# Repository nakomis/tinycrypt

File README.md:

# tinycrypt — a DIY FIDO2 security key you approve from your Apple Watch

## Support

If you find this useful, please consider buying me a coffee:

## Table of Contents

<!-- toc -->
<!-- tocstop -->

## Overview

A YubiKey-style FIDO2/WebAuthn USB security key built on an ESP32-S3, where the "touch the key"
step happens on your wrist instead: the key sends a push notification to an Apple Watch, you tap
**Approve**, and the watch proves it over Bluetooth before the key signs you in.

The first target is signing into AWS IAM Identity Center with the "Security key" MFA option.

**Hardware:**
- ESP32-S3 (target board: Waveshare ESP32-S3-Zero) — native USB, Wi-Fi, BLE
- Microchip ATECC608 — ECC P-256 secure element (I²C) for key storage, added after the software prototype
- Apple Watch — user-presence approval

**Status:** feasibility spikes. Spike A passed: an ESP32-S3 running the
[SoloKeys solo1](https://github.com/solokeys/solo1) CTAP2 core, with an insecure software key and a
BOOT-button presence check, registered and signed into IAM Identity Center from Chrome. The earlier
ATtiny85 / U2F experiments live on the [`spike`](https://github.com/nakomis/tinycrypt/tree/spike) branch.

## How it fits together

1. The browser asks the key (USB HID, CTAP2) for a WebAuthn assertion.
2. The key sends an approval request: AWS IoT Core → SNS → APNs → actionable watch notification (about 2 s).
3. You tap **Approve**; the watch connects to the key over BLE and signs a fresh nonce with its Secure Enclave key.
   The watch must be in Bluetooth range: a remote approval is impossible. On a real watch the Bluetooth exchange takes about 1.4 s after you tap.
4. The key verifies the watch's signature, then signs the WebAuthn assertion and returns it to the browser.

The firmware is split into a portable CTAP2 core with swappable transport, crypto, presence and
notifier back ends, so most of it also runs as a simulator on macOS.

> **Testing builds** can use a software key instead of the ATECC608. That build is deliberately
> insecure, is for testing only, and must only ever be registered against a read-only test user.

## Building and testing

All the firmware lives in `embedded/`, and the commands below run from there. The CTAP2 core is
[SoloKeys solo1](https://github.com/solokeys/solo1) (Apache-2.0 OR MIT), pinned as a submodule in
`embedded/third_party/solo1` under its own licence. Fetch it and the libraries it builds:

```bash
cd embedded
git submodule update --init third_party/solo1
git -C third_party/solo1 submodule update --init crypto/cifra crypto/micro-ecc crypto/tiny-AES-c tinycbor
```

| Path (under `embedded/`) | What it is |
|---|---|
| `cmake/solo_sources.cmake` | The core's source list, shared by both builds |
| `port/` | Portable code: the secure-element interface and solo1's crypto routed through it, presence, the soft element (`TINYCRYPT_INSECURE_SOFT_KEY`, refused in release builds) |
| `sim/` | Mac simulator: CTAPHID over UDP, state in a directory |
| `esp32s3/` | ESP-IDF firmware: TinyUSB FIDO HID, the ATECC608B (or the soft element in NVS), presence, the provisioner |
| `tests/` | python-fido2 tests against the sim, plus `hw_smoke.py` for a real key |

**Mac sim** (needs `brew install libsodium`):

```bash
cmake -S . -B build -DTINYCRYPT_INSECURE_SOFT_KEY=ON && cmake --build build
python3 -m venv tests/.venv && tests/.venv/bin/pip install -r tests/requirements.txt
tests/.venv/bin/python -m pytest tests
build/tinycrypt-sim --presence prompt     # run it by hand; press Enter to approve
```

**ESP32-S3** (ESP-IDF 5.5 in `~/esp/v5.5/esp-idf`):

```bash
esp32s3/build.sh                                    # build (KEYSTORE=atecc for the ATECC608B; soft by default)
esp32s3/build.sh -p /dev/cu.usbmodemXXXX flash      # flash over the UART port
esp32s3/flash-manual.sh /dev/cu.usbmodemXXXX        # if auto-reset fails: hold BOOT, tap RST, release BOOT first
tests/.venv/bin/python tests/hw_smoke.py            # register + authenticate; press BOOT when asked
```

The key enumerates on the S3's **native** USB port (not the UART one) as
"tinycrypt INSECURE TEST KEY", USB ID 303a:4004.

**ATECC608B** (CRYPT-22). Wire a breakout to the dev board: VCC to 3V3, GND, SDA to GPIO38, SCL to
GPIO21 (the PCB's pins; change them under esp-cryptoauthlib in `esp32s3/build.sh menuconfig`). The
breakouts have their own pull-ups. A blank chip answers at 0xC0 (8-bit); the M5Stack Trust&GO unit
(0x6A) is factory-locked and can't take tinycrypt's configuration. Locking is permanent: do a
sacrificial chip first. The provisioner's console is the **native** USB port (USB-Serial-JTAG), so
connect that one; flashing it and the key image straight after needs no BOOT+RST.

```bash
KEYSTORE=atecc esp32s3/build.sh provisioner                 # the provisioner image
ESPTOOL_BEFORE=default_reset esp32s3/flash-manual.sh --provisioner /dev/cu.usbmodemXXXX  # else BOOT+RST first
esp32s3/tools/atecc_provision.py /dev/cu.usbmodemXXXX info
esp32s3/tools/atecc_provision.py /dev/cu.usbmodemXXXX lock  # PERMANENT; asks for the serial
esp32s3/tools/atecc_provision.py /dev/cu.usbmodemXXXX csr tinycrypt-sandbox-key-1 /tmp/key-1.csr
infra/scripts/provision-key.sh key-1 --csr /tmp/key-1.csr   # certificate from the chip's own key
KEYSTORE=atecc esp32s3/build.sh && ESPTOOL_BEFORE=default_reset esp32s3/flash-manual.sh /dev/cu.usbmodemXXXX   # the key again
```

The same steps with the default soft keystore move a key's IoT private key out of `prov` into its
(INSECURE) soft element, with no chip.

## Architecture Diagram

`docs/architecture/tinycrypt.drawio` will be the source for the architecture diagram; the SVG is
auto-regenerated on commit by the pre-commit hook in `.githooks/pre-commit`.

To activate the hook after cloning:

```bash
git config core.hooksPath .githooks
```

## Support

If you find this useful, please consider buying me a coffee:

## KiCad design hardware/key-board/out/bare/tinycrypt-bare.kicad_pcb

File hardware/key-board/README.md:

# tinycrypt key board (CRYPT-16)

The JLCPCB-assembled key: ESP32-S3-MINI-1-N8, ATECC608B, WS2812B-2020, a button and a JST-SH
socket for a captive USB cable. The board is generated by code, from the circuit to the gerbers.
`DESIGN.md` has the parts and the circuit.

## Build

```bash
ASDF_PYTHON_VERSION=3.11.15 python -m venv .venv
.venv/bin/pip install -r requirements.txt
mkdir -p freerouting && cp <somewhere>/freerouting-2.5.0.jar freerouting/   # Java via asdf (25)
./fetch_parts.sh                                       # only if footprints/ is missing or a part is added
.venv/bin/python build.py --board key --route          # full log: /tmp/claude-501/key-board-route.log
.venv/bin/python -m pytest                             # includes one full route (about 15 s)
```

`build.py` writes `out/key/`: `tinycrypt-key.kicad_pcb`, `drc.json`, `bom.csv`, `cpl.csv`,
`tinycrypt-key-gerbers.zip`, the top and bottom renders, and `pins.h`. It writes the fab files only
when KiCad's DRC has no errors and no unconnected items (kicad-cli exits 0 even when DRC fails).
Freerouting isn't deterministic, but it now routes only BUTTON, LED_GPIO and LED_DIN, which are short.

## 3D model (for the case)

```bash
.venv/bin/python build.py --board key --route --step   # also runs ./fetch_models.sh (resumable)
```

`--step` fetches the parts' 3D models (STEP + WRL, about 17 MB, into `footprints/lcsc.3dshapes/`,
gitignored), then writes `out/key/tinycrypt-key.step` (about 9 MB, gitignored; a 1.6 mm board with
its holes and every part's body) and an isometric render, `out/key/tinycrypt-key-3d.png`.

- Every placed part has a body. The WS2812B-2020-V6 has no EasyEDA model, so it uses the WS2812B-2020
  one (C965555): the same 2.0 × 2.0 × 0.82 mm package with the same pad layout.
  The test pads, holes and art have no body.
- `board/parts.py` `MODEL_OFFSET` corrects easyeda2kicad's offsets where they're wrong, found from
  renders: SOT-23-6 and C0603 bodies sat off their pads, the JST body was 2 mm to one side, and the
  capacitors were half inside the board.
- Heights above the board's top face: J1 2.9 mm (the tallest), module 2.4, U4 (SOIC-8) 1.7,
  U3 (SOT-23-6) 1.6, SW1 1.5 (its plunger top), U2 1.1, D1 0.82, C0603 0.8, C0402 0.5, R0402 0.4.
  Nothing on the back, so the bottom is the bare 1.6 mm board.
- The module's antenna overhangs the board edge by 5.04 mm in the model (5.05 mm in the datasheet).

## Pins (for the firmware)

`out/key/pins.h` holds these; `board/key_board.py` (`GPIO`) is the source.

| Signal | GPIO | Module pad |
|---|---|---|
| Button (presence, download strap) | 0 | 4 |
| USB D- / D+ | 19 / 20 | 23 / 24 |
| ATECC608B SDA / SCL (4k7 pull-ups) | 38 / 21 | 34 / 25 |
| WS2812B DIN (through 330R) | 17 | 21 |
| UART0 TX / RX (debug pads) | 43 / 44 | 39 / 40 |

J1 (JST-SH, viewed from the top with its opening facing you, pin 1 on the left):
1 VBUS, 2 D-, 3 D+, 4 CC, 5 GND. Debug pads TP1, from the antenna end: **EN, RX, TX, G, 3V3**.
Bridge EN to G to reset the chip.

## Ordering (JLCPCB)

First order, 16 Oct 2026: 5 boards, all assembled, about £110 with shipping, VAT and baking.

- **Standard PCBA**, not Economic: Economic can't place the ESP32-S3-MINI-1 (pads underneath; X-ray
  inspected) or the 2020 LED, and it allows neither OSP nor yellow. JLCPCB then adds its own edge rails
  (the panel becomes 71 × 71 mm).
- **OSP** finish (cheapest; flat enough for the module), yellow solder mask, white silkscreen (the
  only one on yellow, so Mu is faint; black shows her best). 1.6 mm.
- The BOM matcher may leave U1 (and D1) unticked with quantity 0: tick them. D1 (MSL 5) is baked
  before reflow (accept the pop-up).
- Check the rotations of J1, D1, U1, U2, U3 and U4 in the placement preview. D1 has no 3D model, so
  compare its DI/−/+/DO markers with the pad nets in the `.kicad_pcb` (rotated 180°: DIN top-left,
  GND top-right, 3V3 bottom-left, DOUT bottom-right).
- Most of the price is per order (setup, stencil, a feeder fee per Extended part, X-ray), so 5 boards
  cost little more than 2. Customs description: DIY Hobby Circuit Board. UK VAT is charged at checkout.
- The module's antenna **overhangs the board edge by 5.05 mm on purpose** (marked on Dwgs.User).

## Cable

J1 is a JST **SH 1.0 mm** 5-pin socket: 1 VBUS, 2 D−, 3 D+, 4 CC, 5 GND, the house USB connector
(below). The proper cable is LCSC Cable's custom one (quote requested 16 Oct, PO ref CRYPT-16): a bare
USB-C plug (C393939, no resistor in it) to JST SHR-05V-S-B with SSH-003T-P0.2, UL1571 28 AWG, 150 mm,
wired straight through (VBUS, D−, D+, CC on A5, GND; VCONN unconnected), so it works from any USB-C host
or charger. Off the shelf, a "USB to SH1.0 5P" cable in micro-USB order (VBUS, D−, D+, ID, GND; sold as
"forward wire order") fits as is, its unused ID on pin 4. It's USB-A, so a USB-C host needs a USB-C-to-A (OTG) adapter,
whose plug carries the 5.1 kΩ on CC. Otherwise splice a USB cable to an SH1.0 5-pin pigtail (pigtail
wire colours mean nothing: go by pin position; a USB-C plug needs CC wired to pin 4).

- **Check the cable's pinout with a meter before the first plug-in.** There is no reverse-polarity
  protection. (A breakout's ready-made JST lead turned out to be miswired, SDA on ground.)
- An inline USB power meter on the first plug-in shows 5 V arriving and the current the key draws.

### House USB connector

J1's layout is Martin's house standard for USB on his own boards (16 Oct 2026), so one cable fits them all:

1. **Connector:** JST SM05B-SRSS-TB (SH 1.0 mm, 5-pin, right angle): 1 VBUS, 2 D−, 3 D+, 4 CC, 5 GND,
   printed on the silkscreen.
2. **CC:** one 5.1 kΩ from pin 4 to GND on every board. The cable carries CC straight through, so the
   board's Rd is what makes a USB-C charger or a C-to-C host switch its 5 V on.
3. **Power:** 5 V only (no PD), about 0.5 A in normal use and 1 A at most (the SH crimp's rating). A
   hungrier board gets its own power connector.
4. **Data:** USB 2.0 Full Speed (an S3's native USB, or a USB-serial chip).
5. **Protection:** an ESD array on D+/D−, and on VBUS a polyfuse plus a TVS or reverse-polarity diode
   (this board has neither yet: add them on the next revision).

It stays 5-pin rather than the 4-pin SH order sold as "Type-C to SH1.0 4P" (decided 16 Oct 2026): a 4-pin
cable has to carry the 5.1 kΩ in its plug, and cheap ones often don't (they then work from USB-A only);
their pin orders vary anyway; and a 4-pin SH socket is also Qwiic/STEMMA QT, whose pin 1 is GND, so a USB
lead plugged into one puts 5 V on ground. A 5-pin socket takes neither by mistake.

## Bring-up (each new board, into prod)

Every prod key runs the **secured** variant (CRYPT-34: secure boot v2, flash encryption in release mode,
encrypted NVS). Its first boot burns eFuses for good, after which the key can only be updated over the
air: there's no USB recovery. As first done for `nakomis`, 31 Oct 2026. `NAME` is the key's name (any
lower-case name, e.g. `nakomis`): add it to `prod` in `infra/keys.json` and `pnpm run deploy-prod` first
(that creates the Thing `tinycrypt-prod-NAME`).

1. **Meter the cable** against J1 (1 VBUS, 2 D−, 3 D+, 4 CC or unconnected, 5 GND), and the board's
   3V3 to GND for a short, before the first plug-in. Plug in through the power meter: 5 V, tens of mA.
2. **Provisioner** (PCB pins, so no `BOARD`): hold BTN while plugging in (a blank module enumerates as
   USB-Serial-JTAG), then `KEYSTORE=atecc esp32s3/build.sh provisioner` and
   `esp32s3/flash-manual.sh --provisioner PORT`.
3. `esp32s3/tools/atecc_provision.py PORT info` (a blank 608B: unlocked), `lock` (type the serial),
   then `check` (not `check full`: that's for a sacrificial chip).
4. `atecc_provision.py PORT csr tinycrypt-prod-NAME FILE`, then
   `NPM_ENVIRONMENT=prod AWS_PROFILE=nakom.is-prod infra/scripts/provision-key.sh NAME --csr FILE --no-wifi`.
   No Wi-Fi in `prov`: it's plain NVS, outside flash encryption, so the owner sets Wi-Fi from the iPhone
   app instead (stored in the encrypted NVS). Metrics need the key's vmauth user first (home-servers'
   `vmauth_devices` and SSM `/vmauth/device-tinycrypt-prod-NAME-password`); until then `METRICS_URL=none`.
5. **Secured image:** `NPM_ENVIRONMENT=prod VARIANT=secured KEYSTORE=atecc esp32s3/build.sh` (a fresh
   `build-secured/` if it last held a sandbox build: the bootloader is signed with prod and prod-backup,
   the app with prod). Hold BTN while plugging in, then
   `NPM_ENVIRONMENT=prod esp32s3/flash-manual.sh --secured PORT tinycrypt-prod-NAME` and type the chip's
   MAC. It erases all the flash, writes the bootloader, table, app and `prov`, and reboots into the first
   secure boot (burns secure boot, generates and burns the flash encryption key, encrypts the flash,
   then the app makes and read-protects the NVS key): about 30 s, LED dark. It then enumerates as the
   tinycrypt FIDO device.
6. **Watch and phone:** forget any old entry for this key on the watch, enrol (hold BTN 5 s, "Add key"),
   and give it Wi-Fi from the iPhone app. Check it: `tinycrypt_secured` and `tinycrypt_mqtt` are 1 in
   VictoriaMetrics, `hw_smoke.py` passes.
7. **Fleet:** set the device's firmware project to `tinycrypt-secured`. From then on updates come from
   Fleet prod: CI publishes `tinycrypt-secured` on merge (the bytes the sandbox canary, Kitster, ran).

## As built, against DESIGN.md

- **21 × 34.95 mm.** The board ends at the antenna boundary, so the antenna strip overhangs and
  no keep-out rule area is needed: there's no board under or beside the antenna. The 21 mm width gives
  the 2.8 mm strips beside the module room for the 3V3/EN parts and the debug pads.
- **Mounting holes are off the centre line**, which is the USB path: H1 just past the module, right of
  centre (under Mu's chest on the back, so its ring is masked there and her pixels over the drill are
  dropped); H2 beside J1, on the left.
- **Routing by hand** (`board/key_board.py`): the USB pair (0.2 mm, F.Cu, no stubs); the VBUS and 3V3
  trunks (0.45 mm); EN, RX, TX, SDA, SCL and CC in lanes. The only B.Cu under the USB pair is a
  1.75 mm VBUS hop: U3's VBUS pin sits between D- and D+, so reaching it means crossing one of them.
  3V3 reaches the right half under J1's body, and R2 up the right edge on B.Cu. No B.Cu track crosses
  Mu's face.
- **GND** is left to the pours: the router doesn't route it. Stitching vias sit on a 1 mm grid wherever
  they clear the copper, the silk text and Mu's white fur. A few hand-placed vias tie in pour pockets
  that the tracks close off, and four sit near the antenna-end edge.
- **U1** has a -0.18 mm paste margin on its nine centre pads (about 49 % coverage, against module
  lift) and no thermal vias. Its corner GND pads and U2's GND pin connect to the pour solidly.
- The **button** uses diagonal pads 2 and 3, which are on different contact bars whichever way the
  switch pairs its pins.
- **Parts within 1 mm of a long edge** (exceptions to the rail rule): R2, C6, R4, R5 and the debug
  pads in the right strip, and the mounting-hole rings.
- **22 Ω USB series resistors: not fitted.** They would break the straight hand-routed pair, and Full
  Speed USB doesn't need them.

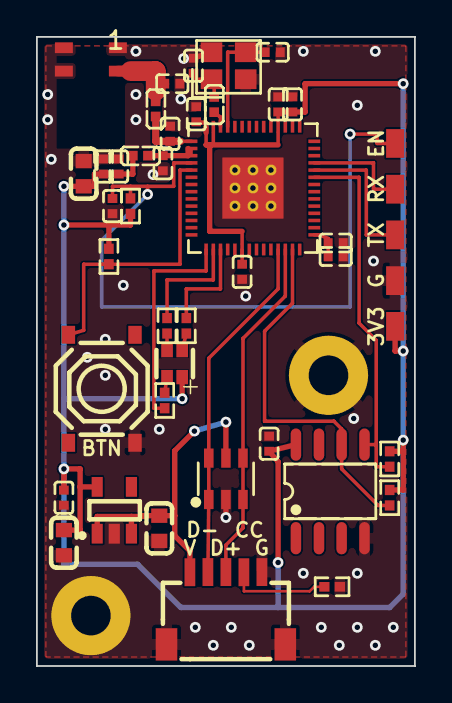
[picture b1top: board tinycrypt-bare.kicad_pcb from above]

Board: 2 copper layers, 21.0 x 35.0 mm, 43 parts (1 on the bottom side), 25 nets.

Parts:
AE1: 2450AT18D0100E; ANT-SMD_4P-L3.2-W1.6
ART1: ART1
C1, C2, C4: 10uF; C0603
C3, C7, C8, C9, C10, C13, C15: 100nF; C0402
C5, C6, C11, C14: 1uF; C0402
C12: 10nF; C0402
C16, C17: 1.5pF; C0402
C18, C19: 15pF; C0402
D1: XL-1615RGBC-RF; LED-ARRAY-SMD_4P-L1.6-W1.5-BR_XL-1615RGBC-RF
H1, H2: M2 hole; MountingHole_M2_2.2mm_Pad4.4
J1: SM05B-SRSS-G-TB; CONN-SMD_SM05B-SRSS-G-TB-LF-SN
L1: 2.0nH; L0402
L2: 2.4nH; L0402
L3: 24nH; L0402
R1: 5k1; R0402
R2, R3: 10k; R0402
R4, R5: 4k7; R0402
R6: 330R; R0402
R7, R8: 100R; R0402
SW1: TS-1187A-B-A-B; SW-SMD_4P-L5.1-W5.1-P3.70-LS6.5-TL_H1.5
TP1: Debug pads; DebugPads_1x5_P2.54
U1: ESP32-S3FN8; QFN-56_ESP32-S3FN8_EP3.4
U2: AP2112K-3.3TRG1; SOT-25-5_L2.9-W1.6-P0.95-LS2.8-BL
U3: USBLC6-2SC6; SOT-23-6_L2.9-W1.6-P0.95-LS2.8-BL
U4: ATECC608B-SSHDA-T; SOIC-8_L4.9-W3.9-P1.27-LS6.0-BL
Y1: 40MHz 10ppm; CRYSTAL-SMD_4P-L2.5-W2.0-BL

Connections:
+3V3: C2.1, C3.1, C4.1, C5.1, C7.1, C8.1, C10.1, C11.1, C12.1, C15.1, D1.2, L1.1, R2.2, R3.2, R4.2, R5.2, TP1.5, U1.20, U1.46, U1.55, U1.56, U2.5, U4.8
BUTTON: R3.1, SW1.2, U1.5
CC: J1.4, R1.1
EN: C6.1, R2.1, TP1.1, U1.4
GND: AE1.1, AE1.2, AE1.3, C1.2, C2.2, C3.2, C4.2, C5.2, C6.2, C7.2, C8.2, C9.2, C10.2, C11.2, C12.2, C13.2, C14.2, C15.2, C16.2, C17.2, C18.2, C19.2, H1.1, H2.1, J1.5, J1.6, J1.7, R1.2, SW1.3, TP1.4, U1.57, U2.2, U3.2, U4.4, Y1.2, Y1.4
LED_B: R8.2, U1.17
LED_BK: D1.3, R8.1
LED_G: R7.2, U1.16
LED_GK: D1.4, R7.1
LED_R: R6.2, U1.15
LED_RK: D1.1, R6.1
LNA_IN: C16.1, L2.1, U1.1
RF_ANT: AE1.4, C17.1, L2.2
SCL: R5.1, U1.27, U4.6
SDA: R4.1, U1.37, U4.5
UART_RX: TP1.2, U1.39
UART_TX: TP1.3, U1.38
USB_DM: J1.2, U1.25, U3.1, U3.6
USB_DP: J1.3, U1.26, U3.3, U3.4
VBUS: C1.1, J1.1, U2.1, U2.3, U3.5
VDD3P3: C9.1, L1.2, U1.2, U1.3
VDD_SPI: C13.1, C14.1, U1.29
XTAL_N: C19.1, U1.53, Y1.3
XTAL_P: L3.1, U1.54
XTAL_PL: C18.1, L3.2, Y1.1

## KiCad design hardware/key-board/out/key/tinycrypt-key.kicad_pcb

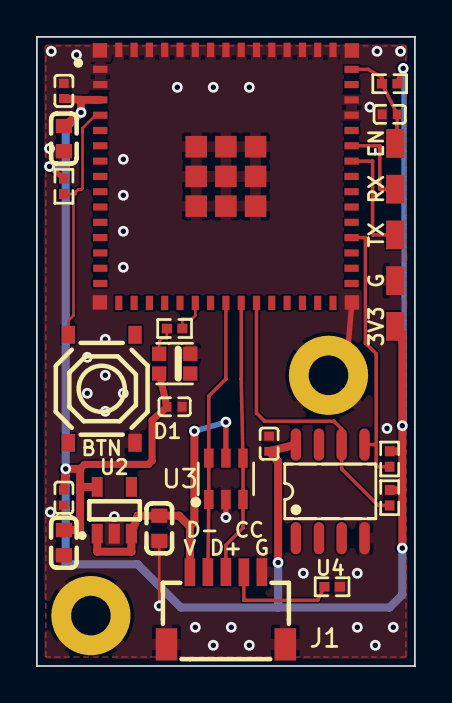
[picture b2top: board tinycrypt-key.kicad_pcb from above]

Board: 2 copper layers, 21.0 x 35.0 mm, 25 parts (1 on the bottom side), 14 nets.

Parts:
ART1: ART1
C1, C2, C4: 10uF; C0603
C3, C5, C7, C8: 100nF; C0402
C6: 1uF; C0402
D1: WS2812B-2020-V6; LED-SMD_4P-L2.2-W2.0-P1.00_WS2815C-2020-4P
H1, H2: M2 hole; MountingHole_M2_2.2mm_Pad4.4
J1: SM05B-SRSS-G-TB; CONN-SMD_SM05B-SRSS-G-TB-LF-SN
R1: 5k1; R0402
R2, R3: 10k; R0402
R4, R5: 4k7; R0402
R6: 330R; R0402
SW1: TS-1187A-B-A-B; SW-SMD_4P-L5.1-W5.1-P3.70-LS6.5-TL_H1.5
TP1: Debug pads; DebugPads_1x5_P2.54
U1: ESP32-S3-MINI-1-N8; BULETM-SMD_ESP32-S3-MINI-1-N8
U2: AP2112K-3.3TRG1; SOT-25-5_L2.9-W1.6-P0.95-LS2.8-BL
U3: USBLC6-2SC6; SOT-23-6_L2.9-W1.6-P0.95-LS2.8-BL
U4: ATECC608B-SSHDA-T; SOIC-8_L4.9-W3.9-P1.27-LS6.0-BL

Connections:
+3V3: C2.1, C3.1, C4.1, C5.1, C7.1, C8.1, D1.4, R2.2, R3.2, R4.2, R5.2, TP1.5, U1.3, U2.5, U4.8
BUTTON: R3.1, SW1.2, U1.4
CC: J1.4, R1.1
EN: C6.1, R2.1, TP1.1, U1.45
GND: C1.2, C2.2, C3.2, C4.2, C5.2, C6.2, C7.2, C8.2, D1.2, H1.1, H2.1, J1.5, J1.6, J1.7, R1.2, SW1.3, TP1.4, U1.1, U1.2, U1.42, U1.43, U1.46, U1.47, U1.48, U1.49, U1.50, U1.51, U1.52, U1.53, U1.54, U1.55, U1.56, U1.57, U1.58, U1.59, U1.60, U1.GND, U2.2, U3.2, U4.4
LED_DIN: D1.3, R6.1
LED_GPIO: R6.2, U1.21
SCL: R5.1, U1.25, U4.6
SDA: R4.1, U1.34, U4.5
UART_RX: TP1.2, U1.40
UART_TX: TP1.3, U1.39
USB_DM: J1.2, U1.23, U3.1, U3.6
USB_DP: J1.3, U1.24, U3.3, U3.4
VBUS: C1.1, J1.1, U2.1, U2.3, U3.5

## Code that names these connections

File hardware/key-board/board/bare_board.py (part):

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HERE = Path(__file__).resolve().parent.parent
W, L = kb.W, kb.L
CX = W / 2
U1_AT = (12.0, 8.4)                  # chip centre; pin 1 (LNA_IN) at its top-left corner
EP_HALF = 1.7                        # the shrunk exposed pad (footprints/local.pretty)
MOAT = 2.4                           # 3V3 runs this far from the chip centre, between pad and pins

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# the USB pair (GPIO21, down the channel beside it) and SDA and the debug UART right-column ones (UART0 is routed through the GPIO matrix: CONFIG_ESP_CONSOLE_UART_CUSTOM;
# only the ROM's first messages still go to U0TXD, which is not wired). None is a strap other than
# GPIO0 (3, 45 and 46 are left alone) or an in-package flash pin (SPI pins 30-35).
GPIO = {"BUTTON": 0, "LED_R": 10, "LED_G": 11, "LED_B": 12, "SDA": 47, "SCL": 21,
        "USB_DM": 19, "USB_DP": 20, "UART_TX": 33, "UART_RX": 34}
# The chip symbol names some GPIOs by their other function, as Espressif's pin table does.
_CHIPPIN = {15: "XTAL_32K_P", 16: "XTAL_32K_N", 39: "MTCK", 40: "MTDO", 41: "MTDI", 42: "MTMS",
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    for pad, net in J1_PINS.items():
        c.connect(net, (j1, pad))
    c.connect(gnd, (j1, "6"), (j1, "7"))
    c.connect("USB_DM", (u3, "1"), (u3, "6"), (u1, gpio_pin(GPIO['USB_DM'])))
    c.connect("USB_DP", (u3, "3"), (u3, "4"), (u1, gpio_pin(GPIO['USB_DP'])))
    c.connect(vbus, (u3, "5"))
    c.connect(gnd, (u3, "2"))
    c.connect(gnd, (c.add("R5K1", "R1"), "2"))
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        c.connect(f"LED_{colour}", (r, "2"), (u1, gpio_pin(GPIO['LED_' + colour])))

    # Debug pads: EN, the console UART (GPIO matrix), GND, 3V3.
    c.connect("UART_TX", (u1, gpio_pin(GPIO['UART_TX'])))
    c.connect("UART_RX", (u1, gpio_pin(GPIO['UART_RX'])))
    for pad, net in DEBUG_PINS.items():
        c.connect(net, (tp, pad))

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    "C17": (7.52, 2.6, 0), "L2": (6.6, 4.0, 90), "C16": (7.4, 5.38, 90),
    # VDDA 10 nF at the corner, beside pin 56
    "C12": (8.85, 4.3, 90),
    # crystal above pins 53/54; L3 inline on XTAL_P; load caps at its two signal pads
    "Y1": (10.65, 1.6, 0), "L3": (9.85, 3.76, 90), "C18": (8.7, 1.6, 90), "C19": (13.1, 0.85, 0),
    # pin 46 (VDD3P3_CPU): 100 nF + 1 uF
    "C10": (13.4, 3.75, 90), "C11": (14.2, 3.75, 90),
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

def rf_hand_route():
    """The antenna feed to pin 1: RF_ANT (antenna pad 4 -> C17 -> L2) at RF_W, necked at the pads;
    LNA_IN (L2 -> C16 -> pin 1), short, 0.4 mm, 0.2 mm into the pin."""
    feed = pad_xy("AE1", "4")
    l2a, l2b = pad_xy("L2", "2"), pad_xy("L2", "1")      # L2 rotated 90: pad 2 up, pad 1 down
    c17 = pad_xy("C17", "1")
    c16 = pad_xy("C16", "1")
    p1 = pin_xy("LNA_IN")
    x = l2a[0]
    t = _seg("RF_ANT", [feed, (feed[0] + 0.7, feed[1])], 0.6)
    t += _seg("RF_ANT", [(feed[0] + 0.7, feed[1]), (x, feed[1]), (x, 3.0)], RF_W)
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

def crystal_hand_route():
    """XTAL_P: pin 54 -> L3 -> Y1 pad 1 (bottom left); XTAL_N: pin 53 straight up between the
    crystal's pad columns into pad 3 (top right). No vias (Espressif)."""
    xp, xn = pin_xy("XTAL_P"), pin_xy("XTAL_N")
    top = xp[1] - 0.33                                    # the pin row's outer edge
    l3a, l3b = pad_xy("L3", "1"), pad_xy("L3", "2")       # L3 at 90: pad 1 down, pad 2 up
    y1p1, y1p3 = pad_xy("Y1", "1"), pad_xy("Y1", "3")
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    pads (x 18.85), to U4 and R4; SCL from GPIO21 alongside D+ and down the channel left of H1,
    under it to U4 and R5 (key_board's SCL route)."""
    t = []
    rx, tx, sda = (pin_xy(gpio_pin(GPIO[k])) for k in ("UART_RX", "UART_TX", "SDA"))
    tp2, tp3 = kb.pad_xy("TP1", "2"), kb.pad_xy("TP1", "3")
    t += _seg("UART_RX", [rx, (18.7, rx[1]), (18.7, tp2[1]), tp2], SIG_W)
    t += _seg("UART_TX", [tx, (18.3, tx[1]), (18.3, tp3[1]), tp3], SIG_W)
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    """The USB pair from pins 25/26 down, then diagonally (0.57 mm apart) into U3's top pins 6/4,
    and from U3's bottom pins into J1, as on key_board. U3's VBUS pin (5) sits between the lines, so
    it hops left across D- on B.Cu."""
    dm0, dp0 = pin_xy(gpio_pin(GPIO['USB_DM'])), pin_xy(gpio_pin(GPIO['USB_DP']))
    u1_, u3_, u4_, u6_ = (kb.pad_xy("U3", n) for n in "1346")
    j2, j3 = kb.pad_xy("J1", "2"), kb.pad_xy("J1", "3")
    ya = 14.0
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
